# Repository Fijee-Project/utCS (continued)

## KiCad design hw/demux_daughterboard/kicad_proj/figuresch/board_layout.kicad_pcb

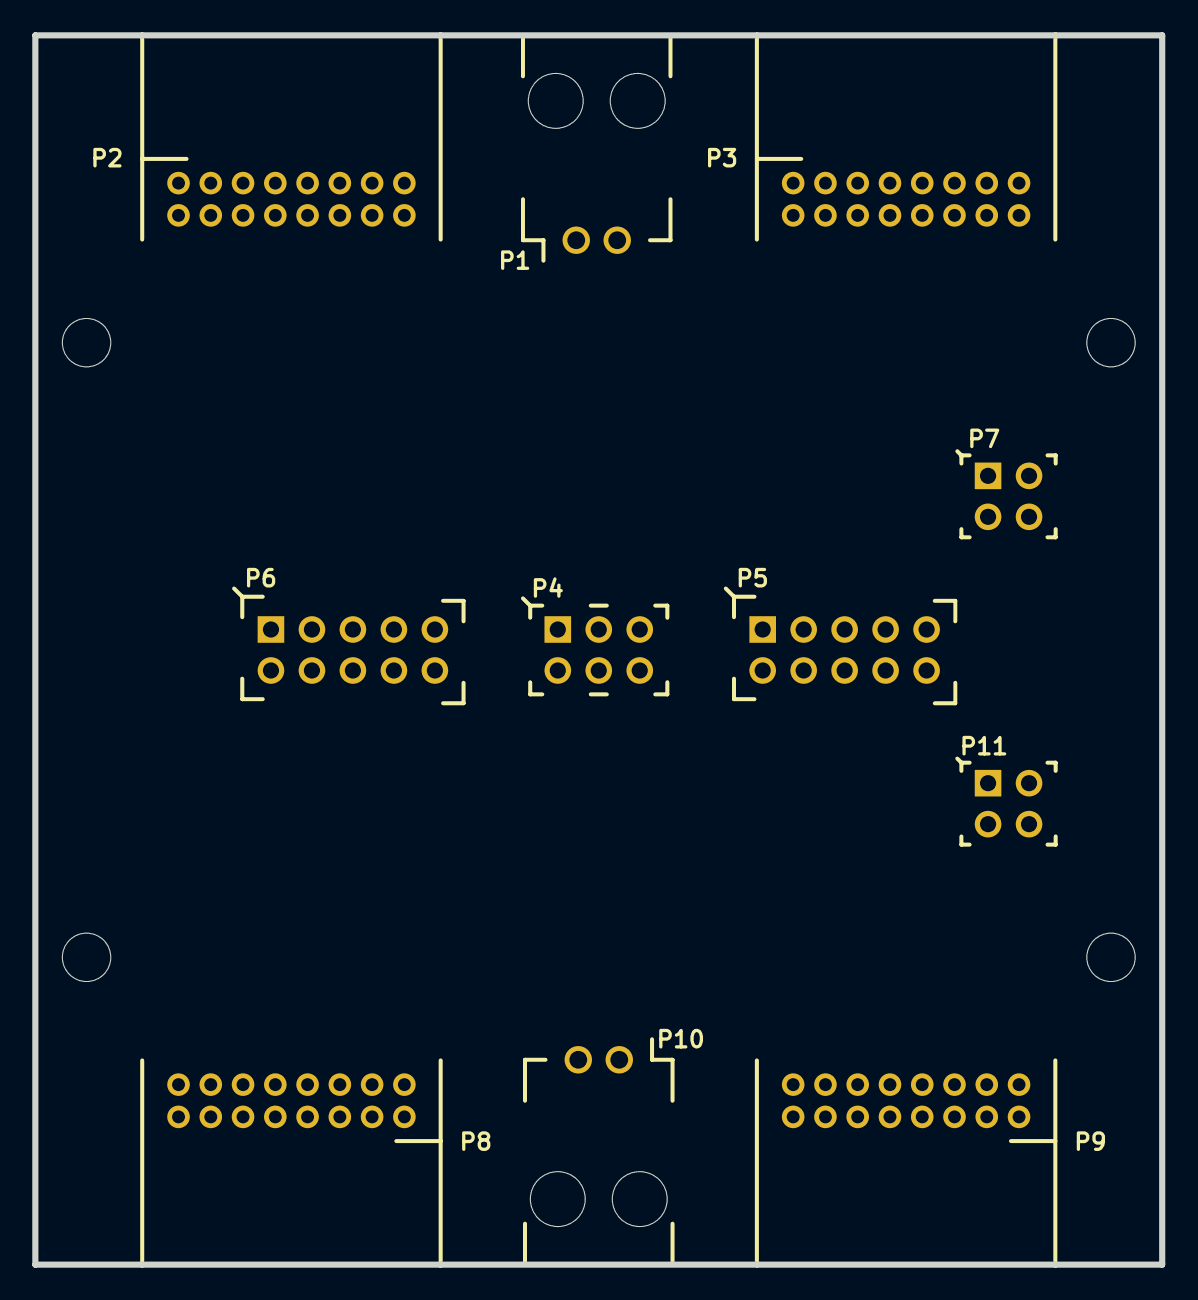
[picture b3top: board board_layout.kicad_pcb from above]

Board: 4 copper layers, 69.8 x 76.2 mm, 15 parts (0 on the bottom side), 16 nets, no tracks yet.

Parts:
P1, P10: CONN_2; CONN_1X2_MOLEX_SL_TH
P2, P3, P8, P9: CONN_8X2; MOLEX_iGRID_2MM_16PIN
P4: CONN_3X2; HEADER-2x3-SAMTEC
P5, P6: CONN_5X2; HEADER-2x5-SAMTEC
P7, P11: CONN_2X2; HEADER-2x2-SAMTEC
SCREW1, SCREW2, SCREW3, SCREW4: CONN_1; SCREW_3mm

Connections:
/A0: P5.10, P6.1
/A1: P5.8, P6.3
/A2: P5.6, P6.5
/A3: P5.4, P6.7
/A4: P5.2, P6.9
/B0: P5.9, P6.2
/B1: P5.7, P6.4
/B2: P5.5, P6.6
/B3: P5.3, P6.8
/B4: P5.1, P6.10
/CS: P4.1, P4.6
/EN: P4.2, P4.5
/WR: P4.3, P4.4
GND: P7.1, P7.2, P7.3, P7.4
VDD: P11.3, P11.4
VSS: P11.1, P11.2

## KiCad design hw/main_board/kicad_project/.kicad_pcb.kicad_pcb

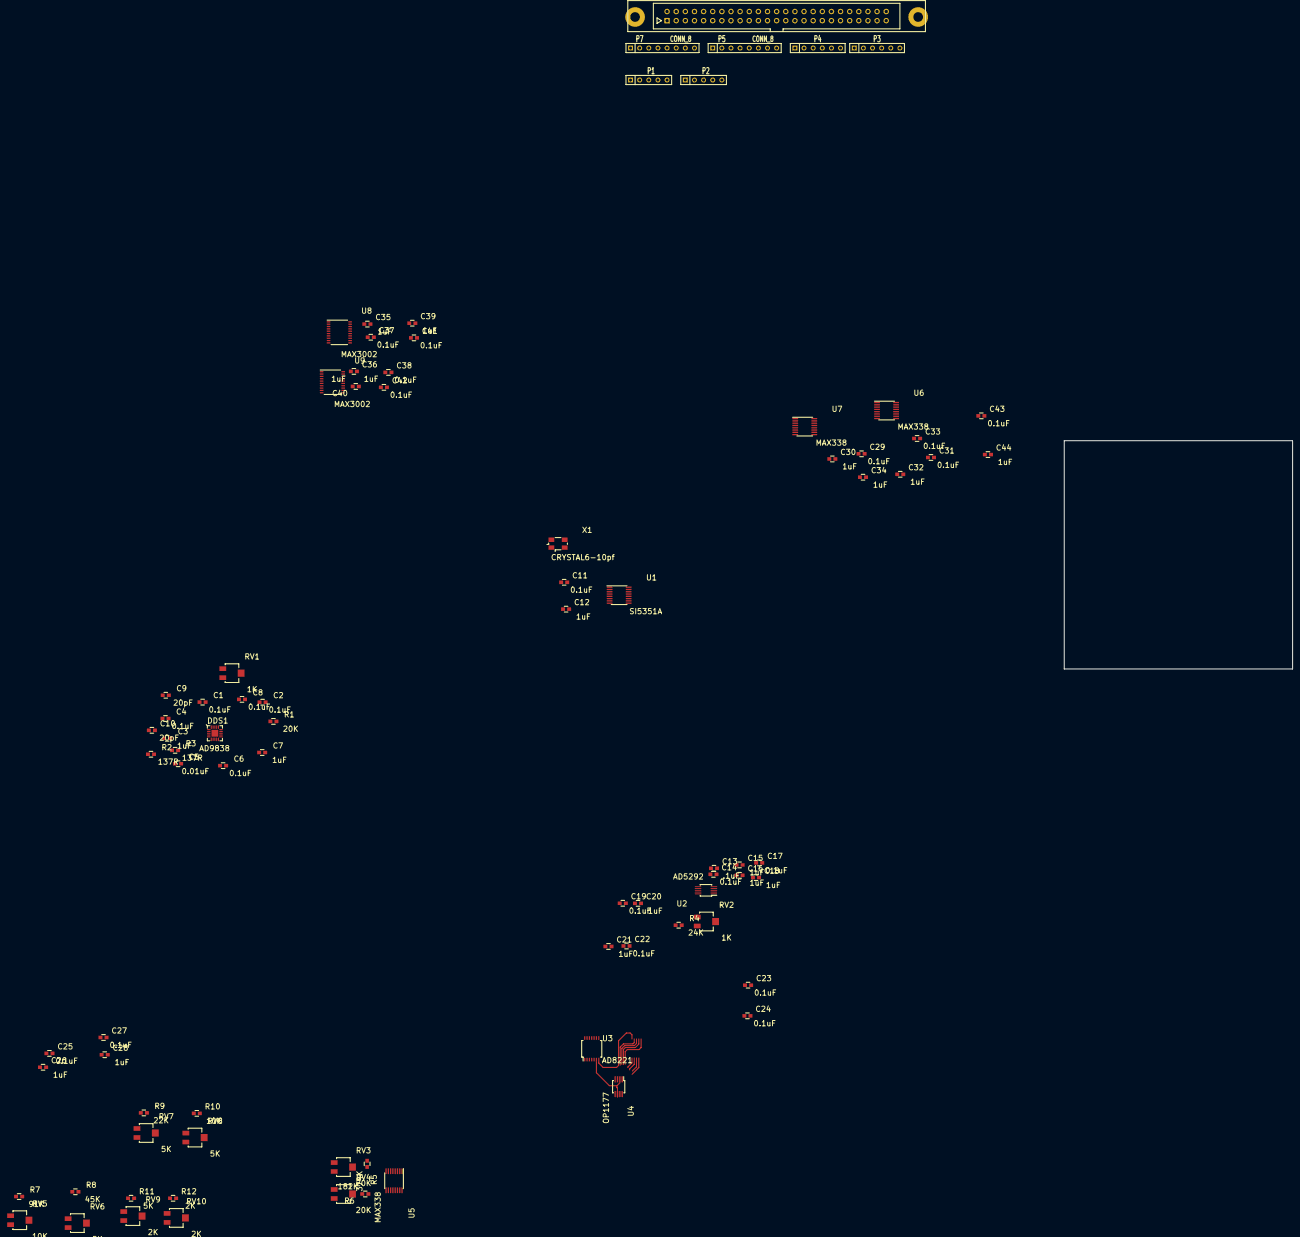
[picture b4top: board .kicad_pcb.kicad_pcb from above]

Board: 4 copper layers, 63.5 x 63.5 mm, 84 parts (0 on the bottom side), 107 nets.

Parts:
C1, C2, C4, C6, C8, C11, C14, C17, C19, C22, C23, C24, C25, C27, C29, C31, C33, C37, C38, C41, C42, C43: 0.1uF; 0603
C3, C7, C12, C15, C16, C18, C20, C21, C26, C28, C30, C32, C34, C35, C36, C39, C40, C44: 1uF; 0603
C5: 0.01uF; 0603
C9, C10: 20pF; 0603
C13: .1uF; 0603
DDS1: AD9838; LFCSP20_WQ
P1, P2: CONN_5; SIL-5
P3: CONN_6; SIL-6
P4: CONN_3X2; SIL-6
P5, P7: CONN_8; SIL-8
P6: CONN_20X2; HE10_50D
R1: 20K; 0603
R2, R3: 137R; 0603
R4: 24K; 0603
R5: 374K; 0603
R6: 182K; 0603
R7: 91K; 0603
R8: 45K; 0603
R9: 22K; 0603
R10: 10K; 0603
R11: 5K; 0603
R12: 2K; 0603
RV1, RV2: 1K; 3224X
RV3, RV4: 20K; 3224X
RV5: 10K; 3224X
RV6, RV7, RV8: 5K; 3224X
RV9, RV10: 2K; 3224X
U1: SI5351A; QSOP_16
U2: AD5292; MSOP-10
U3: AD8221; TSSOP_14
U4: OP1177; MSOP_8
U5, U6, U7: MAX338; QSOP_16
U8, U9: MAX3002; TSSOP_20
X1: CRYSTAL6-10pf; ECX_53B

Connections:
/Clock/CLK_TWI0: P6.8, U1.4
/Clock/CLK_TWI1: P6.10, U1.5
/CurrentSource/AD8211_IOUT: U3.7, U5.8
/CurrentSource/DPOT_A: R4.2, U2.3
/CurrentSource/DPOT_W: RV2.1, RV2.2, U2.4, U2.5
/CurrentSource/GAIN_BUS0: P6.34, U2.1
/CurrentSource/GAIN_BUS1: P6.36, U2.10
/CurrentSource/IOUT: RV3.3, RV4.3, RV5.3, RV6.3, RV7.3, RV8.3, RV9.3, RV10.3, U4.3, U6.8
/CurrentSource/RANGE1: R12.1, U5.4
/CurrentSource/RANGE2: R11.1, U5.5
/CurrentSource/RANGE3: R10.1, U5.6
/CurrentSource/RANGE4: R9.1, U5.7
/CurrentSource/RANGE5: R8.1, U5.9
/CurrentSource/RANGE6: R7.1, U5.10
/CurrentSource/RANGE7: R6.1, U5.11
/CurrentSource/RANGE8: R5.1, U5.12
/CurrentSource/RG2: R4.1, U3.3
/CurrentSource/RNG_0: P6.26, U5.15
/CurrentSource/RNG_1: P6.28, U5.16
/CurrentSource/RNG_2: P6.30, U5.1
/CurrentSource/RNG_3: P6.32, U5.2
/CurrentSource/Rg1: RV2.3, U3.2
/CurrentSource/instr_ref: U3.6, U4.2, U4.6
/DDS/CLK_IN: DDS1.5, U1.10
/DDS/DDS_BUS0: DDS1.10, P6.12
/DDS/DDS_BUS1: DDS1.11, P6.14
/DDS/DDS_BUS2: DDS1.12, P6.16
/DDS/DDS_BUS3: DDS1.6, P6.18
/DDS/DDS_BUS4: DDS1.7, P6.20
/DDS/DDS_BUS5: DDS1.8, P6.22
/DDS/DDS_BUS6: DDS1.9, P6.24
/DDS/VOut: C9.1, DDS1.16, R2.2, U3.4
/DDS/VOut-: C10.1, DDS1.17, R3.2, U3.1
/LogicTranslators/IN_MUX0: P6.31, U6.2
/LogicTranslators/IN_MUX1: P6.33, U6.1
/LogicTranslators/IN_MUX2: P6.35, U6.16
/LogicTranslators/IN_MUX3: P6.37, U6.15
/LogicTranslators/OUT_MUX0: P6.39, U7.2
/LogicTranslators/OUT_MUX1: P6.2, U7.1
/LogicTranslators/OUT_MUX2: P6.4, U7.16
/LogicTranslators/OUT_MUX3: P6.6, U7.15
/LogicTranslators/UCOUT0: P6.1, U8.1
/LogicTranslators/UCOUT1: P6.3, U8.3
/LogicTranslators/UCOUT2: P6.5, U8.4
/LogicTranslators/UCOUT3: P6.7, U8.5
/LogicTranslators/UCOUT4: P6.9, U8.6
/LogicTranslators/UCOUT5: P6.11, U8.7
/LogicTranslators/UCOUT6: P6.13, U8.8
/LogicTranslators/UCOUT7: P6.15, U8.9
/LogicTranslators/UCOUT8: P6.17, U8.10
/LogicTranslators/UCOUT9: P6.19, U9.10
/LogicTranslators/UCOUT10: P6.21, U9.9
/LogicTranslators/UCOUT11: P6.23, U9.8
/LogicTranslators/UCOUT12: P6.25, U9.7
/LogicTranslators/UCOUT13: P6.27, U9.6
/LogicTranslators/UCOUT14: P6.29, U9.5
/MUXC0: P1.1, U8.20
/MUXC1: P1.2, U8.18
/MUXC2: P1.3, U8.17
/MUXC3: P1.4, U8.16
/MUXC4: P1.5, U8.15
/MUXCOM0: P3.5, U8.12
/MUXCOM1: P3.3, U8.13
/MUXCOM2: P3.2, U8.14
/MUXD0: P2.1, U9.12
/MUXD1: P2.2, U9.13
/MUXD2: P2.3, U9.14
/MUXD3: P2.4, U9.15
/MUXD4: P2.5, U9.16
/OutputMultiplexer/MUXA0: P7.1, U6.12
/OutputMultiplexer/MUXA1: P7.2, U7.12
/OutputMultiplexer/MUXA2: P7.3, U6.11
/OutputMultiplexer/MUXA3: P7.4, U7.11
/OutputMultiplexer/MUXA4: P7.5, U6.10
/OutputMultiplexer/MUXA5: P7.6, U7.10
/OutputMultiplexer/MUXA6: P7.7, U6.9
/OutputMultiplexer/MUXA7: P7.8, U7.9
/OutputMultiplexer/MUXB0: P5.1, U6.4
/OutputMultiplexer/MUXB1: P5.2, U7.4
/OutputMultiplexer/MUXB2: P5.3, U6.5
/OutputMultiplexer/MUXB3: P5.4, U7.5
/OutputMultiplexer/MUXB4: P5.5, U6.6
/OutputMultiplexer/MUXB5: P5.6, U7.6
/OutputMultiplexer/MUXB6: P5.7, U6.7
/OutputMultiplexer/MUXB7: P5.8, U7.7
/powergen/MUXVSS: P3.6, P4.2
AGND: C1.2, C2.2, C3.1, C4.1, C6.1, C7.1, C8.1, C9.2, C10.2, C11.2, C12.2, C13.2, C14.2, C15.2, C16.2, C17.2, C18.2, C19.2, C20.2, C21.2, C22.2, C23.2, C24.2, C25.2, C26.2, C27.2, C28.2, C29.2, C30.2, C31.2, C32.2, C33.2, C34.2, C35.2, C36.2, C37.2, C38.2, C39.2, C40.2, C41.2, C42.2, C43.2, C44.2, DDS1.4, DDS1.15, P3.4, P4.4, R2.1, R3.1, RV1.3, U2.9, U5.14, U6.14, U7.8, U7.14, U8.11, U9.11
AVDD: C17.1, C18.1, C19.1, C20.1, C23.1, C25.1, C26.1, C29.1, C30.1, C33.1, C34.1, P4.5, U2.6, U3.8, U4.7, U5.3, U6.13, U7.13
AVDD_3V3: C1.1, C3.2, C5.2, C6.2, C7.2, C11.1, C12.1, C16.1, C39.1, C40.1, C41.1, C42.1, DDS1.1, DDS1.2, P4.3, U1.1, U1.7, U2.8, U8.2, U9.2
AVSS: C14.1, C15.1, C21.1, C22.1, C24.1, C27.1, C28.1, C31.1, C32.1, C43.1, C44.1, P4.6, U2.2, U3.5, U4.4, U5.13, U6.3, U7.3
DVDD_2V5: C35.1, C36.1, C37.1, C38.1, P3.1, P4.1, U8.19, U9.19
unnamed: C2.1, DDS1.19
unnamed: C4.2, DDS1.3
unnamed: C5.1, DDS1.20
unnamed: C8.2, DDS1.18, R1.1
unnamed: R1.2, RV1.1, RV1.2
unnamed: R9.2, RV7.1, RV7.2
unnamed: R5.2, RV3.1, RV3.2
unnamed: R6.2, RV4.1, RV4.2
unnamed: R8.2, RV6.1, RV6.2
unnamed: R7.2, RV5.1, RV5.2
unnamed: R10.2, RV8.1, RV8.2
unnamed: R11.2, RV9.1, RV9.2
unnamed: R12.2, RV10.1, RV10.2
unnamed: C13.1, U2.7
unnamed: U1.3, X1.2
unnamed: U1.2, X1.1

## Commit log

2014-01-31 initial commit.
2014-02-01 Basic Directory Structure
2014-02-01 design draft documentation add, some gitignores
2014-02-01 added initial board files
2014-02-01 folder restructuring
2014-02-27 PWR_board hierarchy added
2014-02-27 setting folder structure TODO: remove .empty's once folders are populated
2014-02-27 initial eagle library for eventual project port
2014-02-27 initial set of datasheets in doc/datasheets/
2014-02-28 keepnote notebook included to keep track of all design calculations
2014-02-28 custom kicad library for main board, fleshing out notes
2014-03-01 Main board module library, added SOIC-8, MSOP-8, MSOP-10, SOIC-10, other landing patterns, almost done
2014-03-01 added tssop 20 to main modules
2014-03-01 finalized all footprints for main board, need to pick connectors and finalize stacking desing
2014-03-01 working on gain control, added some schematics for document figure use only
2014-03-04 refactored schematic, finalized gain/range
2014-03-05 starting power supply design, still collecting notes
2014-03-05 minor cleanup
2014-03-07 started mainboard pcb layout, fixing small things in schematic, TODO: schematic connector symbols and pads
2014-03-10 Cleaned up main board component library
2014-03-10 more doc updates
2014-03-11 started mainboard pcb assembly
2014-03-12 connectors for main_pcb still deciding on proper footprint/layout
2014-03-15 started reworking modules and layout for daughterboard
2014-03-16 final rework of mux board, finalizing stacking connectors, almost there
2014-03-17 Finished daughterboard pcb with fusion pcb constraints, TODO: silkscreen
2014-03-18 daughterboard silkscreen finalized, gerbers generated for 1.0RevA
2014-03-20 finished component layout on mainboard, need to route power planes and the digital control signal lines
2014-03-29 finished board and gerber outputed, time for documentation
2014-04-01 Converting keepnote notes to thorough design documentation, starting with BRD1
2014-04-02 more work on BRFD1 design doc
2014-04-02 forgot to add files in last commit
2014-06-06 local changes to notes and most production gerber file
